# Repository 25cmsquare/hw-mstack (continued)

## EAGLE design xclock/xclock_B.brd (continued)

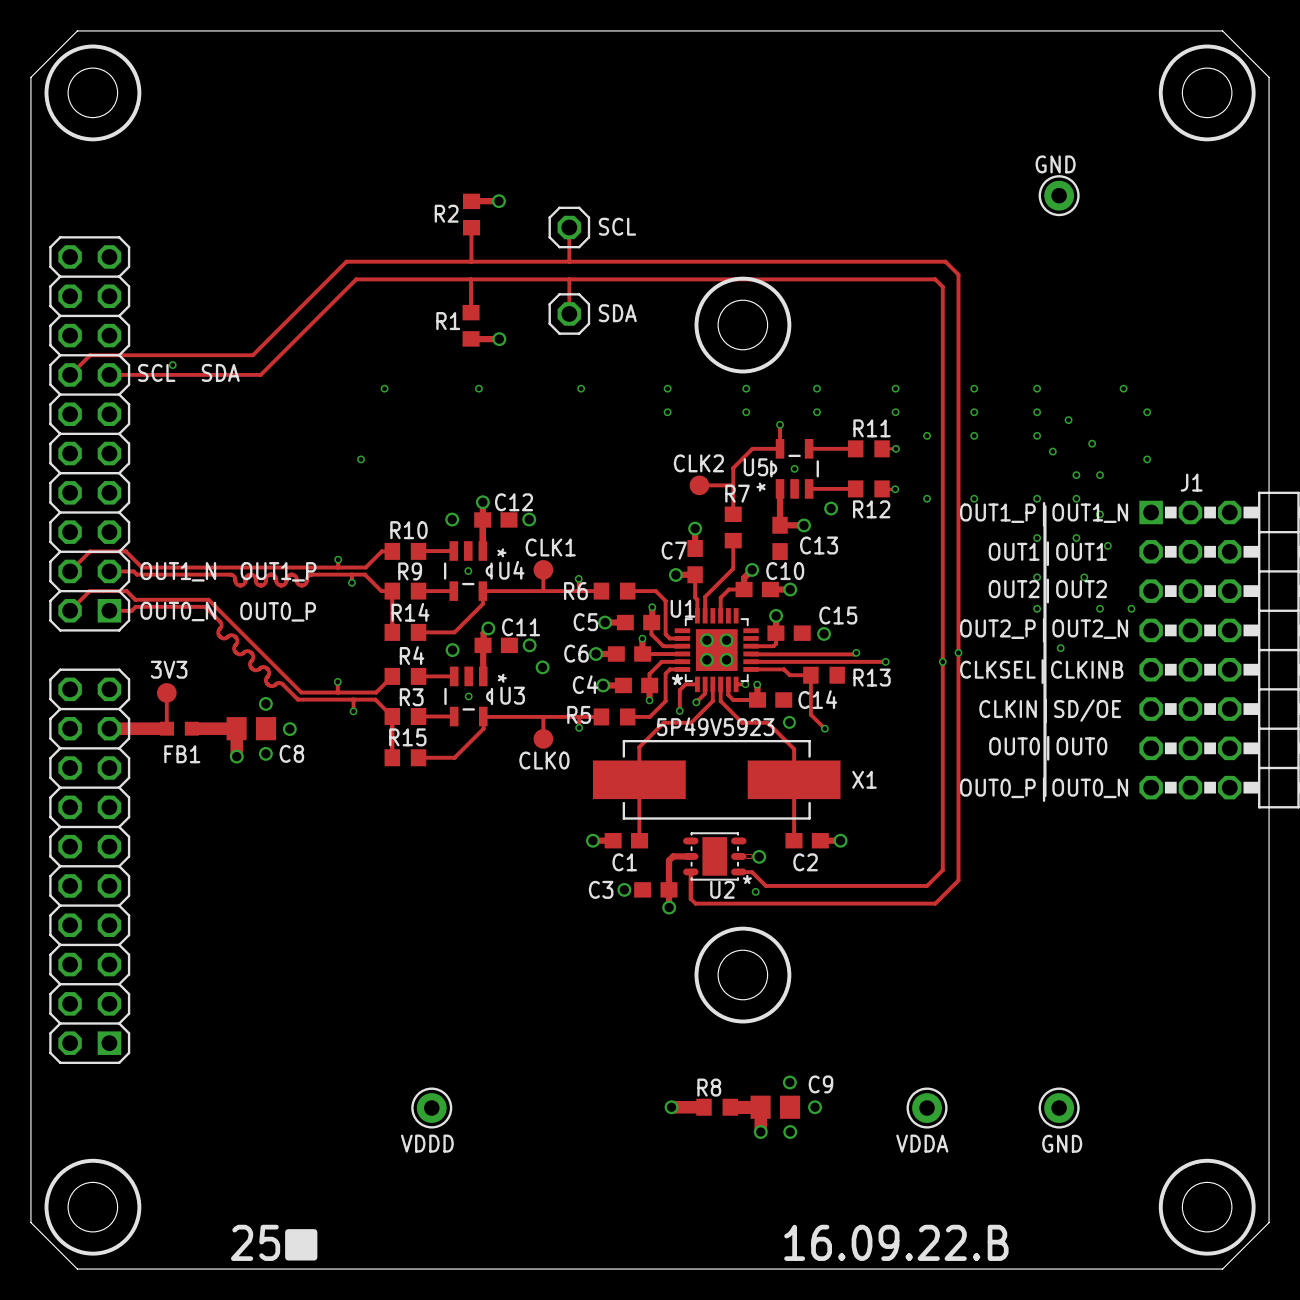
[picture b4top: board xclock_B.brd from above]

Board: 4 copper layers, 80.0 x 80.0 mm, 49 parts (0 on the bottom side), 30 nets.

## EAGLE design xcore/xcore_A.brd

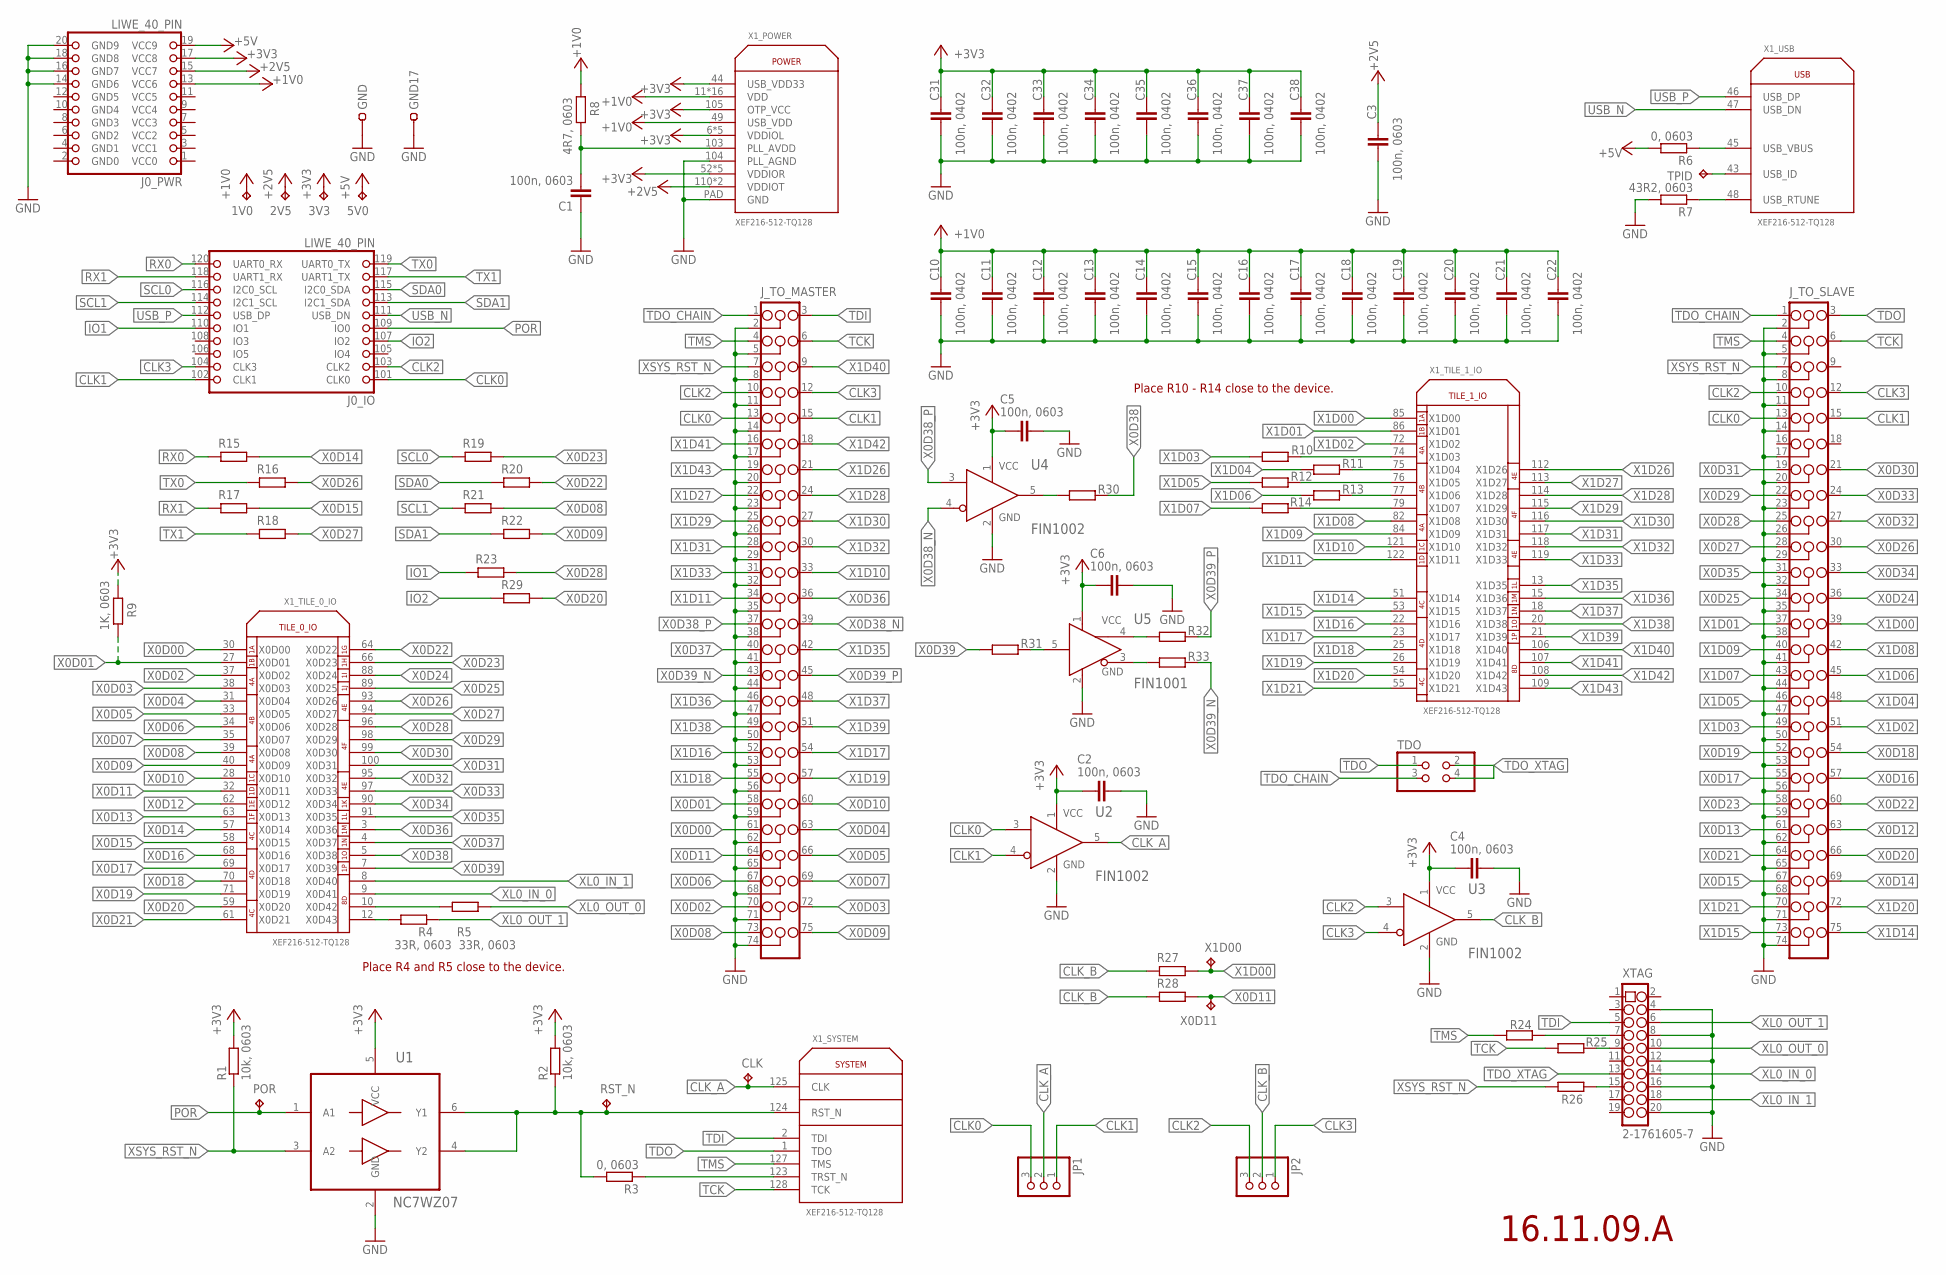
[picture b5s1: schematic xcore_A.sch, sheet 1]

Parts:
1V0, 2V5, 3V3, 5V0: TPTP14R; TP14R
C1, C2, C4, C5, C6: 100n, 0603; C0603
C3: 100n, 0603; C0402K
C10, C11, C12, C13, C14, C15, C16, C17, C18, C19, C20, C21, C22, C31, C32, C33, C34, C35, C36, C37, C38: 100n, 0402; C0402K
CLK: TPTP14R; TP14R
GND, GND17: TEST-22-MULTICOMP; TEST_1MM
J0: LIWE_40_PIN; LIWE_40_PIN_8X8
JP1, JP2: PINHD-1X3; 1X03
J_TO_MASTER: TSW-125-08-G-T-RA; 3X25/90/M
J_TO_SLAVE: TSW-125-08-G-T-RA; 3X25/90
POR: TPTP14R; TP14R
R1, R2: 10k, 0603; R0603
R3, R6: 0, 0603; R0603
R4, R5: 33R, 0603; R0603
R7: 43R2, 0603; R0603
R8: 4R7, 0603; R0603
R9: 1K, 0603; R0603
R10, R11, R12, R13, R14, R15, R16, R17, R18, R19, R20, R21, R22, R23, R24, R25, R26, R27, R28, R29, R30, R31, R32, R33: R-EU_R0603; R0603
RST_N: TPTP14R; TP14R
TDO: PINHD-2X2; 2X02
TPID: TPB1,27; B1,27
U1: NC7WZ07; SOT65P210X110-6N
U2, U3, U4: FIN1002; SOT95P280X140-5N
U5: FIN1001; SOT95P280X140-5N
X0D11, X1D00: TPTP14R; TP14R
X1: XEF216-512-TQ128; TQFP128
XTAG: 2-1761605-7; 2X10

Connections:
+1V0: 1V0.TP, C10.2, C11.2, C12.2, C13.2, C14.2, C15.2, C16.2, C17.2, C18.2, C19.2, C20.2, C21.2, C22.2, J0.13 (VCC6), R8.1, X1.11 (VDD), X1.16 (VDD), X1.17 (VDD), X1.24 (VDD), X1.36 (VDD), X1.41 (VDD), X1.49 (USB_VDD), X1.56 (VDD), X1.60 (VDD), X1.73 (VDD), X1.80 (VDD), X1.81 (VDD), X1.87 (VDD), X1.101 (VDD), X1.102 (VDD), X1.120 (VDD), X1.126 (VDD)
+2V5: 2V5.TP, C3.2, J0.15 (VCC7), X1.110 (VDDIOT), X1.111 (VDDIOT)
+3V3: 3V3.TP, C2.2, C4.2, C5.2, C6.2, C31.2, C32.2, C33.2, C34.2, C35.2, C36.2, C37.2, C38.2, J0.17 (VCC8), R1.2, R2.2, R9.1, U1.5 (VCC), U2.1 (VCC), U3.1 (VCC), U4.1 (VCC), U5.1 (VCC), X1.6 (VDDIOL), X1.14 (VDDIOL), X1.19 (VDDIOL), X1.29 (VDDIOL), X1.42 (VDDIOL), X1.44 (USB_VDD33), X1.52 (VDDIOR), X1.67 (VDDIOR), X1.78 (VDDIOR), X1.83 (VDDIOR), X1.92 (VDDIOR), X1.105 (OTP_VCC)
+5V: 5V0.TP, J0.19 (VCC9), R6.2
CLK0: J0.101 (CLK0), JP1.3, J_TO_MASTER.13, J_TO_SLAVE.13, U2.3 (RIN+)
CLK1: J0.102 (CLK1), JP1.1, J_TO_MASTER.15, J_TO_SLAVE.15, U2.4 (RIN-)
CLK2: J0.103 (CLK2), JP2.3, J_TO_MASTER.10, J_TO_SLAVE.10, U3.3 (RIN+)
CLK3: J0.104 (CLK3), JP2.1, J_TO_MASTER.12, J_TO_SLAVE.12, U3.4 (RIN-)
CLK_A: CLK.TP, JP1.2, U2.5 (ROUT), X1.125 (CLK)
CLK_B: JP2.2, R27.1, R28.1, U3.5 (ROUT)
GND: C1.1, C2.1, C3.1, C4.1, C5.1, C6.1, C10.1, C11.1, C12.1, C13.1, C14.1, C15.1, C16.1, C17.1, C18.1, C19.1, C20.1, C21.1, C22.1, C31.1, C32.1, C33.1, C34.1, C35.1, C36.1, C37.1, C38.1, GND.1, GND17.1, J0.14 (GND6), J0.16 (GND7), J0.18 (GND8), J0.20 (GND9), J_TO_MASTER.2, J_TO_MASTER.5, J_TO_MASTER.8, J_TO_MASTER.11, J_TO_MASTER.14, J_TO_MASTER.17, J_TO_MASTER.20, J_TO_MASTER.23, J_TO_MASTER.26, J_TO_MASTER.29, J_TO_MASTER.32, J_TO_MASTER.35, J_TO_MASTER.38, J_TO_MASTER.41, J_TO_MASTER.44, J_TO_MASTER.47, J_TO_MASTER.50, J_TO_MASTER.53, J_TO_MASTER.56, J_TO_MASTER.59, J_TO_MASTER.62, J_TO_MASTER.65, J_TO_MASTER.68, J_TO_MASTER.71, J_TO_MASTER.74, J_TO_SLAVE.2, J_TO_SLAVE.5, J_TO_SLAVE.8, J_TO_SLAVE.11, J_TO_SLAVE.14, J_TO_SLAVE.17, J_TO_SLAVE.20, J_TO_SLAVE.23, J_TO_SLAVE.26, J_TO_SLAVE.29, J_TO_SLAVE.32, J_TO_SLAVE.35, J_TO_SLAVE.38, J_TO_SLAVE.41, J_TO_SLAVE.44, J_TO_SLAVE.47, J_TO_SLAVE.50, J_TO_SLAVE.53, J_TO_SLAVE.56, J_TO_SLAVE.59, J_TO_SLAVE.62, J_TO_SLAVE.65, J_TO_SLAVE.68, J_TO_SLAVE.71, J_TO_SLAVE.74, R7.2, U1.2 (GND), U2.2 (GND), U3.2 (GND), U4.2 (GND), U5.2 (GND), X1.104 (PLL_AGND), X1.PAD (GND), XTAG.4, XTAG.8, XTAG.12, XTAG.16, XTAG.20
IO1: J0.110 (IO1), R23.1
IO2: J0.107 (IO2), R29.1
unnamed: R10.2, X1.74 (X1D03)
unnamed: R11.2, X1.75 (X1D04)
unnamed: R12.2, X1.76 (X1D05)
unnamed: R13.2, X1.77 (X1D06)
unnamed: R14.2, X1.79 (X1D07)
unnamed: R30.1, U4.5 (ROUT)
unnamed: R31.2, U5.5 (RIN)
unnamed: R32.1, U5.4 (ROUT+)
unnamed: R33.1, U5.3 (ROUT-)
PLL_AVDD: C1.2, R8.2, X1.103 (PLL_AVDD)
POR: J0.109 (IO0), POR.TP, U1.1 (A1)
RST_N: R2.1, R3.2, RST_N.TP, U1.4 (Y2), U1.6 (Y1), X1.124 (RST_N)
RX0: J0.120 (UART0_RX), R15.1
RX1: J0.118 (UART1_RX), R17.1
SCL0: J0.116 (I2C0_SCL), R19.1
SCL1: J0.114 (I2C1_SCL), R21.1
SDA0: J0.115 (I2C0_SDA), R20.1
SDA1: J0.113 (I2C1_SDA), R22.1
TCK: J_TO_MASTER.6, J_TO_SLAVE.6, R25.1, X1.128 (TCK)
TCK_: R25.2, XTAG.9
TDI: J_TO_MASTER.3, X1.2 (TDI), XTAG.5
TDO: J_TO_SLAVE.3, TDO.1, X1.1 (TDO)
TDO_CHAIN: J_TO_MASTER.1, J_TO_SLAVE.1, TDO.3
TDO_XTAG: TDO.2, TDO.4, XTAG.13
TMS: J_TO_MASTER.4, J_TO_SLAVE.4, R24.1, X1.127 (TMS)
TMS_: R24.2, XTAG.7
TRST_N: R3.1, X1.123 (TRST_N)
TX0: J0.119 (UART0_TX), R16.1
TX1: J0.117 (UART1_TX), R18.1
USB_ID: TPID.TP, X1.43 (USB_ID)
USB_N: J0.111 (USB_DN), X1.47 (USB_DN)
USB_P: J0.112 (USB_DP), X1.46 (USB_DP)
USB_RTUNE: R7.1, X1.48 (USB_RTUNE)
USB_VBUS: R6.1, X1.45 (USB_VBUS)
X0D00: J_TO_MASTER.61, X1.30 (X0D00)
X0D01: J_TO_MASTER.58, R9.2, X1.27 (X0D01)
X0D02: J_TO_MASTER.70, X1.37 (X0D02)
X0D03: J_TO_MASTER.72, X1.38 (X0D03)
X0D04: J_TO_MASTER.63, X1.31 (X0D04)
X0D05: J_TO_MASTER.66, X1.33 (X0D05)
X0D06: J_TO_MASTER.67, X1.34 (X0D06)
X0D07: J_TO_MASTER.69, X1.35 (X0D07)
X0D08: J_TO_MASTER.73, R21.2, X1.39 (X0D08)
X0D09: J_TO_MASTER.75, R22.2, X1.40 (X0D09)
X0D10: J_TO_MASTER.60, X1.28 (X0D10)
X0D11: J_TO_MASTER.64, R28.2, X0D11.TP, X1.32 (X0D11)
X0D12: J_TO_SLAVE.63, X1.62 (X0D12)
X0D13: J_TO_SLAVE.61, X1.63 (X0D13)
X0D14: J_TO_SLAVE.69, R15.2, X1.57 (X0D14)
X0D15: J_TO_SLAVE.67, R17.2, X1.58 (X0D15)
X0D16: J_TO_SLAVE.57, X1.68 (X0D16)
X0D17: J_TO_SLAVE.55, X1.69 (X0D17)
X0D18: J_TO_SLAVE.54, X1.70 (X0D18)
X0D19: J_TO_SLAVE.52, X1.71 (X0D19)
X0D20: J_TO_SLAVE.66, R29.2, X1.59 (X0D20)
X0D21: J_TO_SLAVE.64, X1.61 (X0D21)
X0D22: J_TO_SLAVE.60, R20.2, X1.64 (X0D22)
X0D23: J_TO_SLAVE.58, R19.2, X1.66 (X0D23)
X0D24: J_TO_SLAVE.36, X1.88 (X0D24)
X0D25: J_TO_SLAVE.34, X1.89 (X0D25)
X0D26: J_TO_SLAVE.30, R16.2, X1.93 (X0D26)
X0D27: J_TO_SLAVE.28, R18.2, X1.94 (X0D27)
X0D28: J_TO_SLAVE.25, R23.2, X1.96 (X0D28)
X0D29: J_TO_SLAVE.22, X1.98 (X0D29)
X0D30: J_TO_SLAVE.21, X1.99 (X0D30)
X0D31: J_TO_SLAVE.19, X1.100 (X0D31)
X0D32: J_TO_SLAVE.27, X1.95 (X0D32)
X0D33: J_TO_SLAVE.24, X1.97 (X0D33)
X0D34: J_TO_SLAVE.33, X1.90 (X0D34)
X0D35: J_TO_SLAVE.31, X1.91 (X0D35)
X0D36: J_TO_MASTER.36, X1.3 (X0D36)
X0D37: J_TO_MASTER.40, X1.4 (X0D37)
X0D38: R30.2, X1.5 (X0D38)
X0D38_N: J_TO_MASTER.39, U4.4 (RIN-)
X0D38_P: J_TO_MASTER.37, U4.3 (RIN+)
X0D39: R31.1, X1.7 (X0D39)
X0D39_N: J_TO_MASTER.43, R33.2
X0D39_P: J_TO_MASTER.45, R32.2
X0D42: R5.2, X1.10 (X0D42)
X0D43: R4.2, X1.12 (X0D43)
X1D00: J_TO_SLAVE.39, R27.2, X1.85 (X1D00), X1D00.TP
X1D01: J_TO_SLAVE.37, X1.86 (X1D01)
X1D02: J_TO_SLAVE.51, X1.72 (X1D02)
X1D03: J_TO_SLAVE.49, R10.1
X1D04: J_TO_SLAVE.48, R11.1
X1D05: J_TO_SLAVE.46, R12.1
X1D06: J_TO_SLAVE.45, R13.1
X1D07: J_TO_SLAVE.43, R14.1
X1D08: J_TO_SLAVE.42, X1.82 (X1D08)
X1D09: J_TO_SLAVE.40, X1.84 (X1D09)
X1D10: J_TO_MASTER.33, X1.121 (X1D10)
X1D11: J_TO_MASTER.34, X1.122 (X1D11)
X1D14: J_TO_SLAVE.75, X1.51 (X1D14)
X1D15: J_TO_SLAVE.73, X1.53 (X1D15)
X1D16: J_TO_MASTER.52, X1.22 (X1D16)
X1D17: J_TO_MASTER.54, X1.23 (X1D17)
X1D18: J_TO_MASTER.55, X1.25 (X1D18)
X1D19: J_TO_MASTER.57, X1.26 (X1D19)
X1D20: J_TO_SLAVE.72, X1.54 (X1D20)
X1D21: J_TO_SLAVE.70, X1.55 (X1D21)
X1D26: J_TO_MASTER.21, X1.112 (X1D26)
X1D27: J_TO_MASTER.22, X1.113 (X1D27)
X1D28: J_TO_MASTER.24, X1.114 (X1D28)
X1D29: J_TO_MASTER.25, X1.115 (X1D29)
X1D30: J_TO_MASTER.27, X1.116 (X1D30)
X1D31: J_TO_MASTER.28, X1.117 (X1D31)
X1D32: J_TO_MASTER.30, X1.118 (X1D32)
X1D33: J_TO_MASTER.31, X1.119 (X1D33)
X1D35: J_TO_MASTER.42, X1.13 (X1D35)
X1D36: J_TO_MASTER.46, X1.15 (X1D36)
X1D37: J_TO_MASTER.48, X1.18 (X1D37)
X1D38: J_TO_MASTER.49, X1.20 (X1D38)
X1D39: J_TO_MASTER.51, X1.21 (X1D39)
X1D40: J_TO_MASTER.9, X1.106 (X1D40)
X1D41: J_TO_MASTER.16, X1.107 (X1D41)
X1D42: J_TO_MASTER.18, X1.108 (X1D42)
X1D43: J_TO_MASTER.19, X1.109 (X1D43)
XL0_IN_0: X1.9 (X0D41), XTAG.14
XL0_IN_1: X1.8 (X0D40), XTAG.18
XL0_OUT_0: R5.1, XTAG.10
XL0_OUT_1: R4.1, XTAG.6
XSYS_RST_N: J_TO_MASTER.7, J_TO_SLAVE.7, R1.1, R26.1, U1.3 (A2)
XSYS_RST_N_: R26.2, XTAG.15

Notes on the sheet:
16.11.09.A
Place R4 and R5 close to the device.
Place R10 - R14 close to the device.

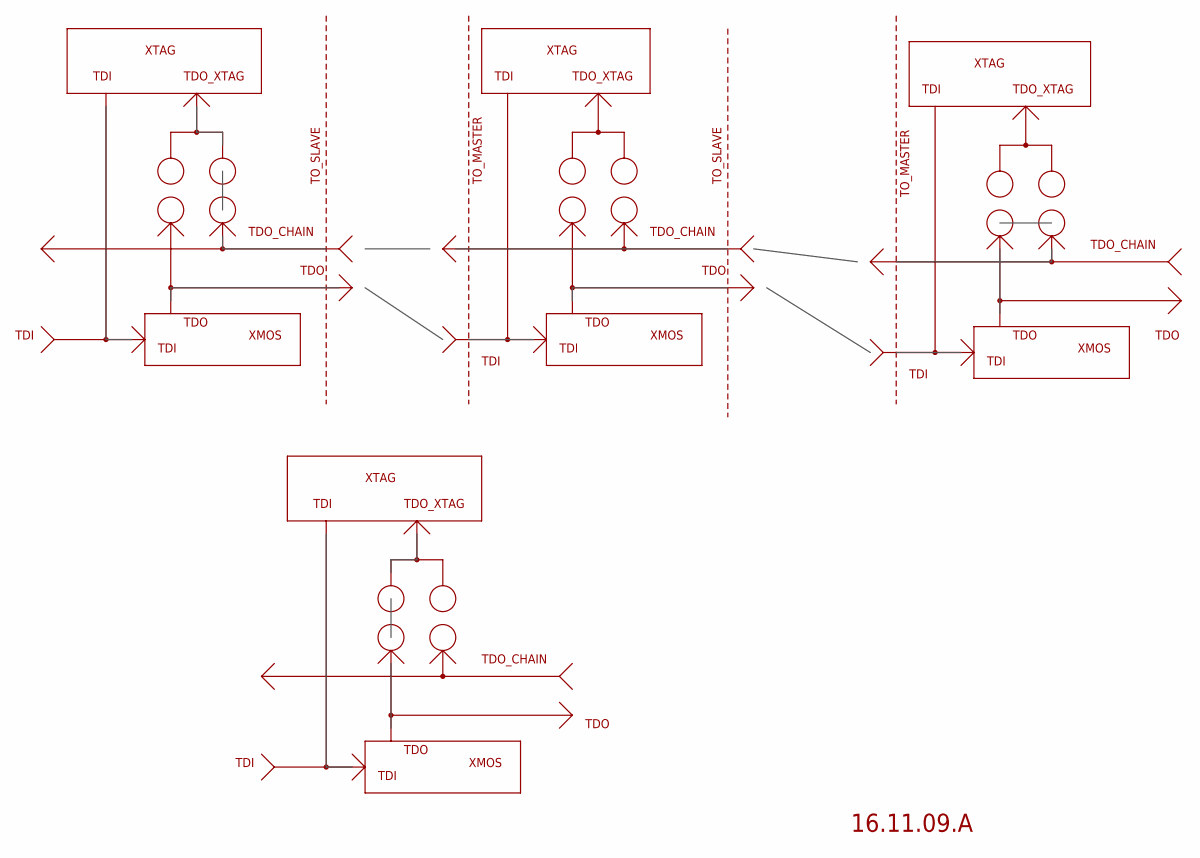
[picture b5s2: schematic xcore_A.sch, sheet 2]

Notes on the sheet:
16.11.09.A
XTAG
XMOS
TDO_XTAG
TDI
TDO
TDO_CHAIN
TO_SLAVE
TO_MASTER

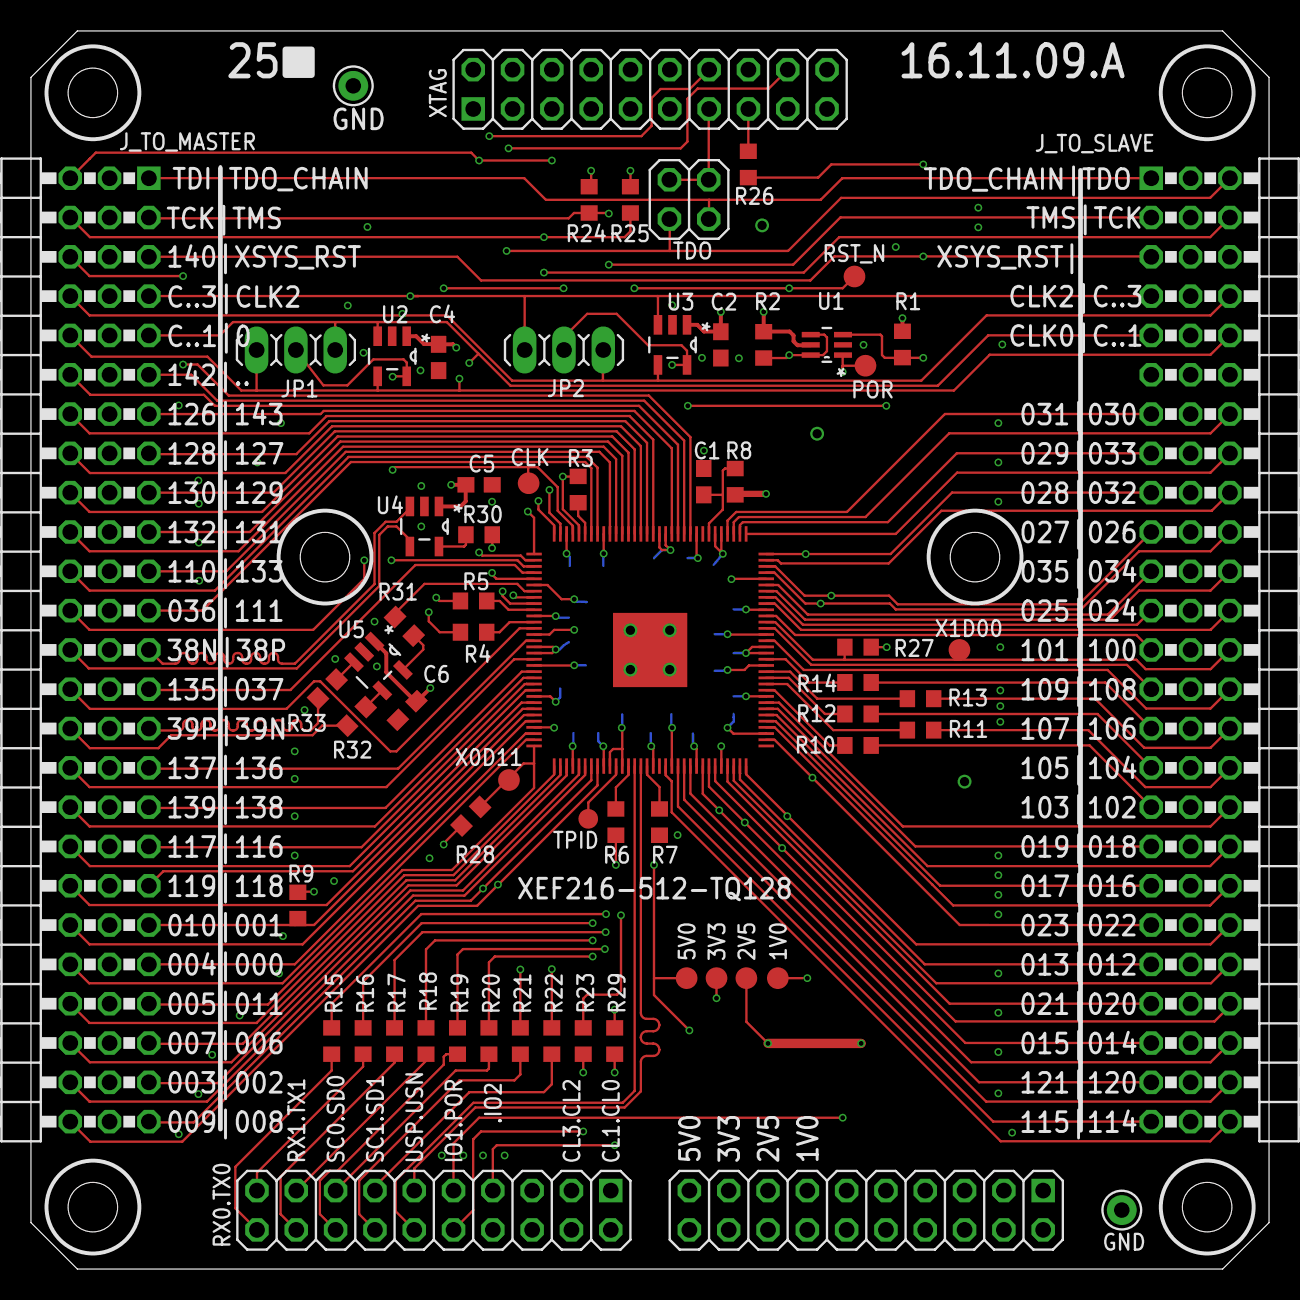
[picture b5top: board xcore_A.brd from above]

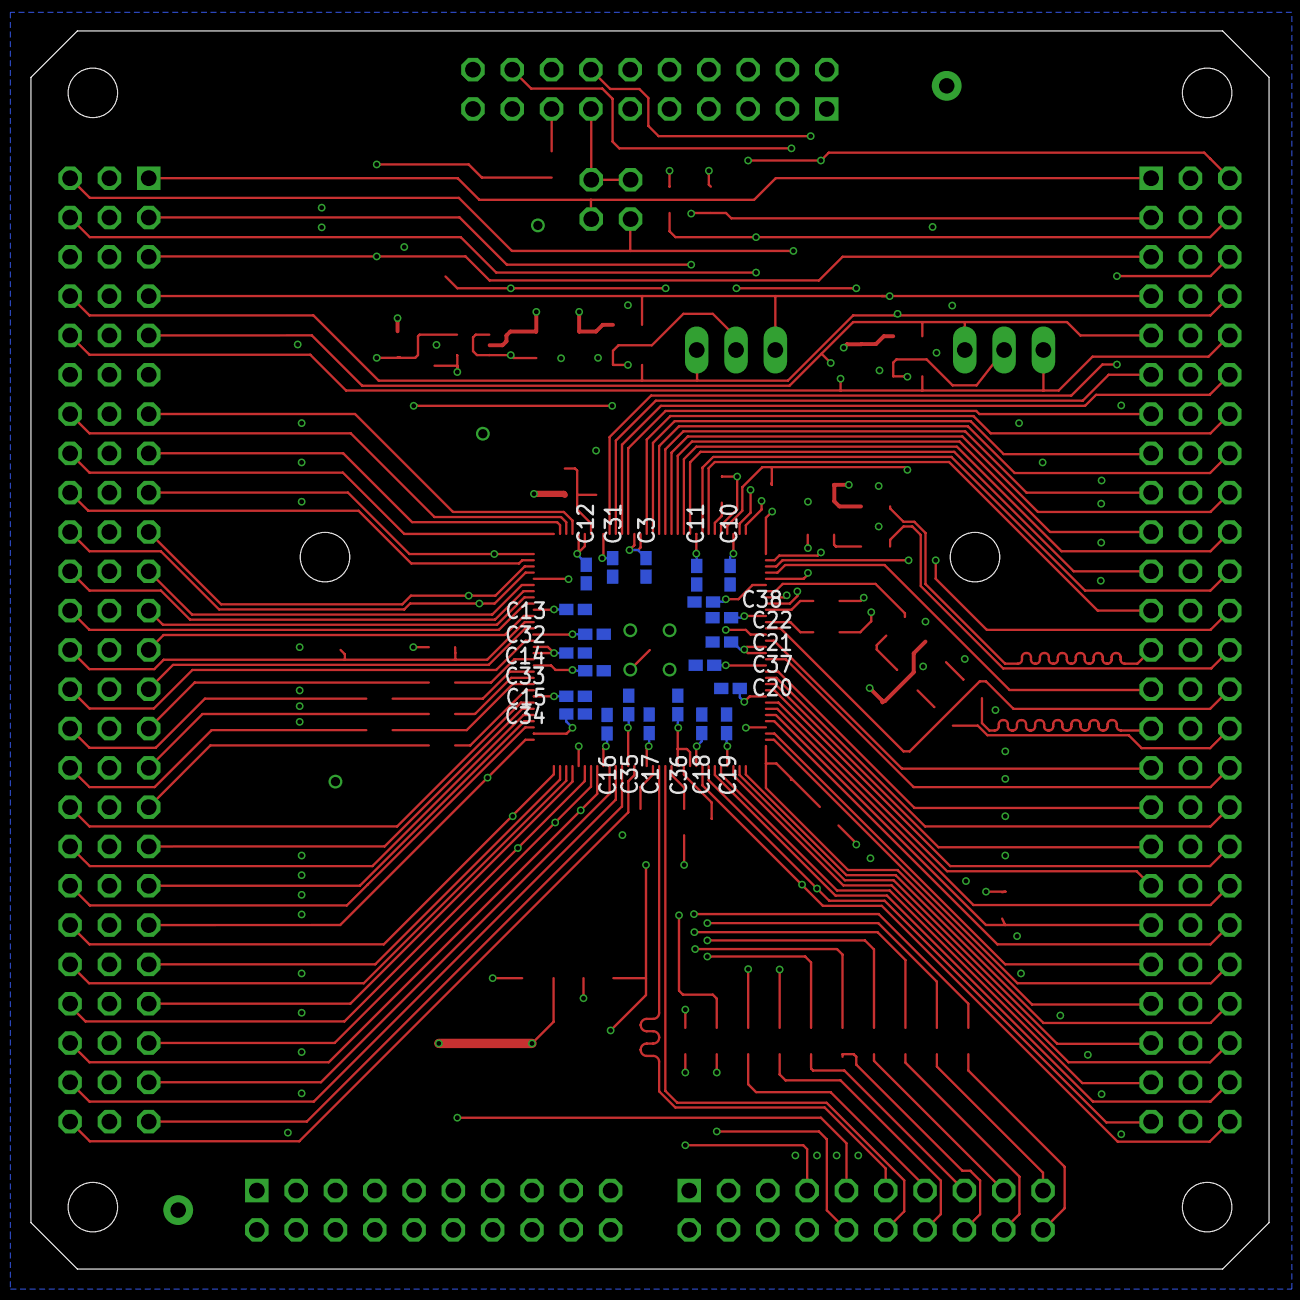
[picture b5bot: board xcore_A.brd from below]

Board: 4 copper layers, 80.0 x 80.0 mm, 85 parts (22 on the bottom side), 136 nets.

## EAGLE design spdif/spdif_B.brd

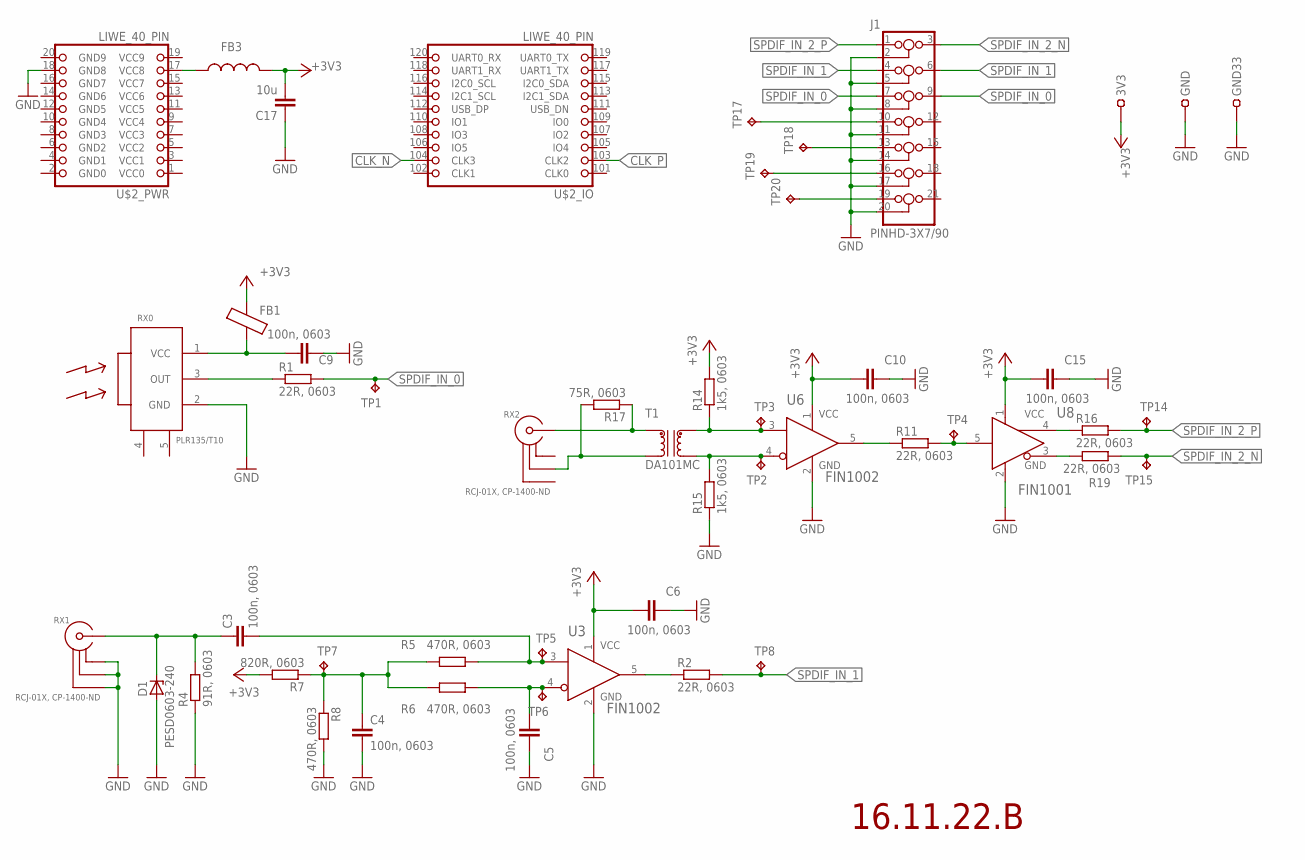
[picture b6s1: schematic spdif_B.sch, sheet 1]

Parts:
3V3: TEST-22-MULTICOMP; TEST_1MM
C3, C4, C5, C6, C9, C10, C15: 100n, 0603; C0603
C17: 10u; C0805
D1: PESD0603-240; L0603
FB1: FB_0603; L0603
FB3: L0603(1608); L0603
GND, GND33: TEST-22-MULTICOMP; TEST_1MM
J1: PINHD-3X7/90; 3X07/90
R1, R2, R11, R16, R19: 22R, 0603; R0603
R4: 91R, 0603; R0603
R5, R6, R8: 470R, 0603; R0603
R7: 820R, 0603; R0603
R14, R15: 1k5, 0603; R0603
R17: 75R, 0603; R0603
RX0: PLR135/T10; PLR135_T10
RX1, RX2: RCJ-01X, CP-1400-ND; RCJ-01X
T1: DA101MC
TP1, TP2, TP3, TP4, TP5, TP6, TP7, TP8, TP14, TP15, TP17, TP18, TP19, TP20: TPB1,27; B1,27
U3, U6: FIN1002; SOT95P280X140-5N
U8: FIN1001; SOT95P280X140-5N
U$2: LIWE_40_PIN; LIWE_40_PIN_8X8

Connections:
+3V3: 3V3.1, C6.2, C10.2, C15.2, C17.2, FB1.2, FB3.2, R7.2, R14.2, U3.1 (VCC), U6.1 (VCC), U8.1 (VCC); also elsewhere on the board
CLK_N: U$2.104 (CLK3); also elsewhere on the board
CLK_P: U$2.103 (CLK2); also elsewhere on the board
GND: C4.2, C5.1, C6.1, C9.1, C10.1, C15.1, C17.1, D1.1 (A), GND.1, GND33.1, J1.2, J1.5, J1.8, J1.11, J1.14, J1.17, J1.20, R4.1, R8.2, R15.1, RX0.2 (GND), RX1.20 (GND1), RX1.21 (GND2), RX1.22 (GND3), U3.2 (GND), U6.2 (GND), U8.2 (GND), U$2.18 (GND8); also elsewhere on the board
unnamed: R11.2, TP4.TP, U8.5 (RIN)
unnamed: R16.1, U8.4 (ROUT+)
unnamed: R2.1, U3.5 (ROUT)
unnamed: C3.2, R5.1, TP5.TP, U3.3 (RIN+)
unnamed: C9.2, FB1.1, RX0.1 (VCC)
unnamed: C3.1, D1.2 (C), R4.2, RX1.1 (SIG)
unnamed: R19.1, U8.3 (ROUT-)
unnamed: C4.1, R5.2, R6.2, R7.1, R8.1, TP7.TP
unnamed: C5.2, R6.1, TP6.TP, U3.4 (RIN-)
unnamed: J1.10, TP17.TP
unnamed: R15.2, T1.4, TP2.TP, U6.4 (RIN-)
unnamed: R14.1, T1.6, TP3.TP, U6.3 (RIN+)
unnamed: J1.13, TP18.TP
unnamed: J1.16, TP19.TP
unnamed: R17.2, RX2.21 (GND2), T1.3
unnamed: R17.1, RX2.1 (SIG), T1.1
unnamed: J1.19, TP20.TP
unnamed: FB3.1, U$2.17 (VCC8)
SPDIF0_IN: R1.1, RX0.3 (OUT)
SPDIF_IN_0: J1.7, J1.9, R1.2, TP1.TP
SPDIF_IN_1: J1.4, J1.6, R2.2, TP8.TP
SPDIF_IN_2_N: J1.3, R19.2, TP15.TP
SPDIF_IN_2_P: J1.1, R16.2, TP14.TP
U6_OUT: R11.1, U6.5 (ROUT)

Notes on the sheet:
16.11.22.B

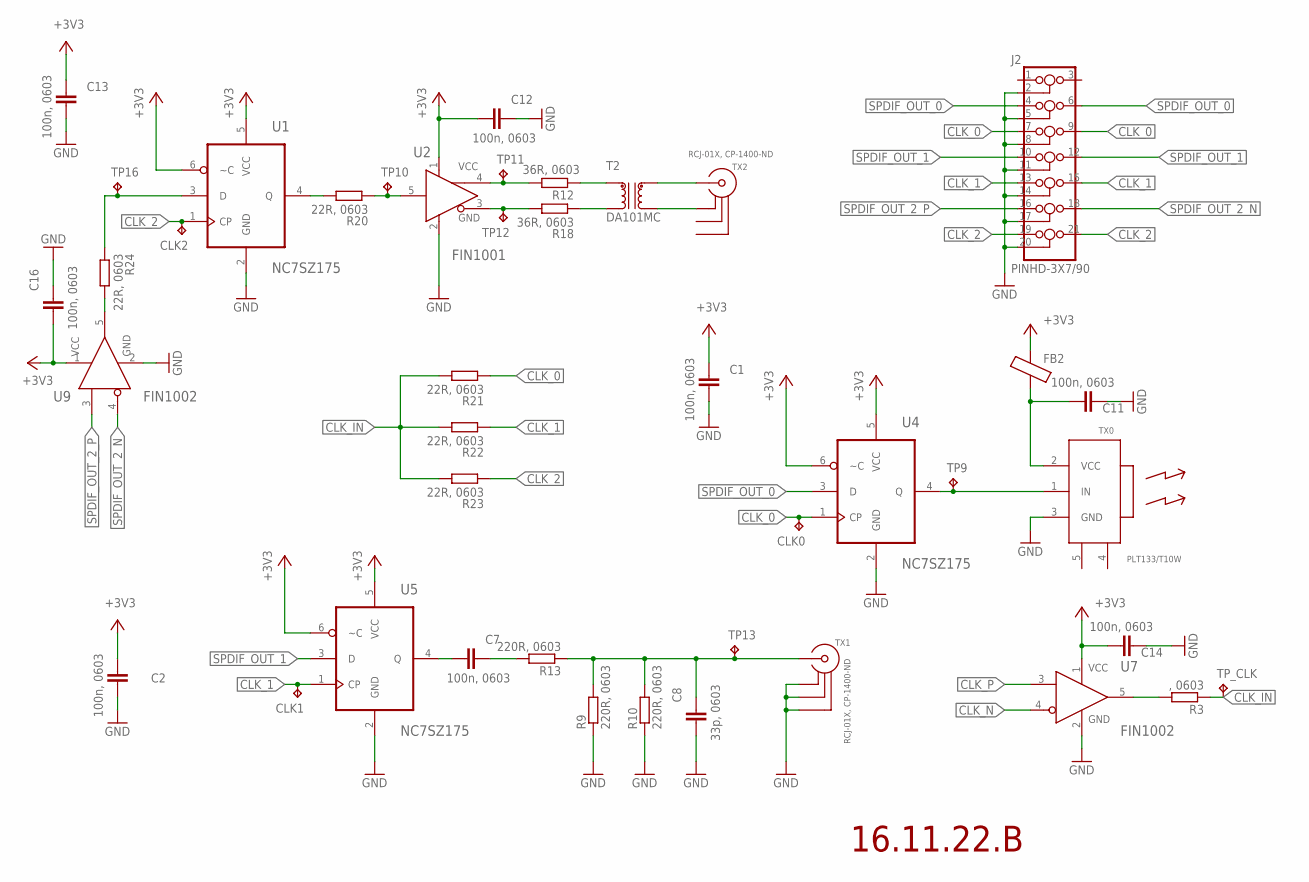
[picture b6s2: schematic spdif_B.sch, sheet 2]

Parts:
C1, C2, C7, C11, C12, C13, C14, C16: 100n, 0603; C0603
C8: 33p, 0603; C0603
CLK0, CLK1, CLK2: TPB1,27; B1,27
FB2: FB_0603; L0603
J2: PINHD-3X7/90; 3X07/90
R3: , 0603; R0603
R9, R10, R13: 220R, 0603; R0603
R12, R18: 36R, 0603; R0603
R20, R21, R22, R23, R24: 22R, 0603; R0603
T2: DA101MC
TP9, TP10, TP11, TP12, TP13, TP16: TPB1,27; B1,27
TP_CLK: TPB1,27; B1,27
TX0: PLT133/T10W; PLT133_T10W
TX1, TX2: RCJ-01X, CP-1400-ND; RCJ-01X
U1, U4, U5: NC7SZ175; SOT65P210X110-6N
U2: FIN1001; SOT95P280X140-5N
U7, U9: FIN1002; SOT95P280X140-5N

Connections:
+3V3: C1.2, C2.2, C12.2, C13.2, C14.2, C16.2, FB2.2, U1.5 (VCC), U1.6 (~C), U2.1 (VCC), U4.5 (VCC), U4.6 (~C), U5.5 (VCC), U5.6 (~C), U7.1 (VCC), U9.1 (VCC); also elsewhere on the board
CLK_0: CLK0.TP, J2.7, J2.9, R21.1, U4.1 (CP)
CLK_1: CLK1.TP, J2.13, J2.15, R22.1, U5.1 (CP)
CLK_2: CLK2.TP, J2.19, J2.21, R23.1, U1.1 (CP)
CLK_IN: R3.1, R21.2, R22.2, R23.2, TP_CLK.TP
CLK_N: U7.4 (RIN-); also elsewhere on the board
CLK_P: U7.3 (RIN+); also elsewhere on the board
DA_N: R18.1, T2.3
DA_P: R12.1, T2.1
FIN_IN: R20.1, TP10.TP, U2.5 (RIN)
FIN_OUT_N: R18.2, TP12.TP, U2.3 (ROUT-)
FIN_OUT_P: R12.2, TP11.TP, U2.4 (ROUT+)
GND: C1.1, C2.1, C8.2, C11.1, C12.1, C13.1, C14.1, C16.1, J2.2, J2.5, J2.8, J2.11, J2.14, J2.17, J2.20, R9.1, R10.1, TX0.3 (GND), TX1.20 (GND1), TX1.21 (GND2), TX1.22 (GND3), U1.2 (GND), U2.2 (GND), U4.2 (GND), U5.2 (GND), U7.2 (GND), U9.2 (GND); also elsewhere on the board
unnamed: R24.2, U9.5 (ROUT)
unnamed: R3.2, U7.5 (ROUT)
unnamed: R24.1, TP16.TP, U1.3 (D)
unnamed: C7.1, R13.2
unnamed: C7.2, U5.4 (Q)
Q: R20.2, U1.4 (Q)
SPDIF_OUT_0: J2.4, J2.6, U4.3 (D)
SPDIF_OUT_1: J2.10, J2.12, U5.3 (D)
SPDIF_OUT_2_N: J2.18, U9.4 (RIN-)
SPDIF_OUT_2_P: J2.16, U9.3 (RIN+)
TX0_IN: TP9.TP, TX0.1 (IN), U4.4 (Q)
TX0_VCC: C11.2, FB2.1, TX0.2 (VCC)
TX1_IN: C8.1, R9.2, R10.2, R13.1, TP13.TP, TX1.1 (SIG)
TX2_N: T2.4, TX2.20 (GND1)
TX2_P: T2.6, TX2.1 (SIG)

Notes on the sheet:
16.11.22.B

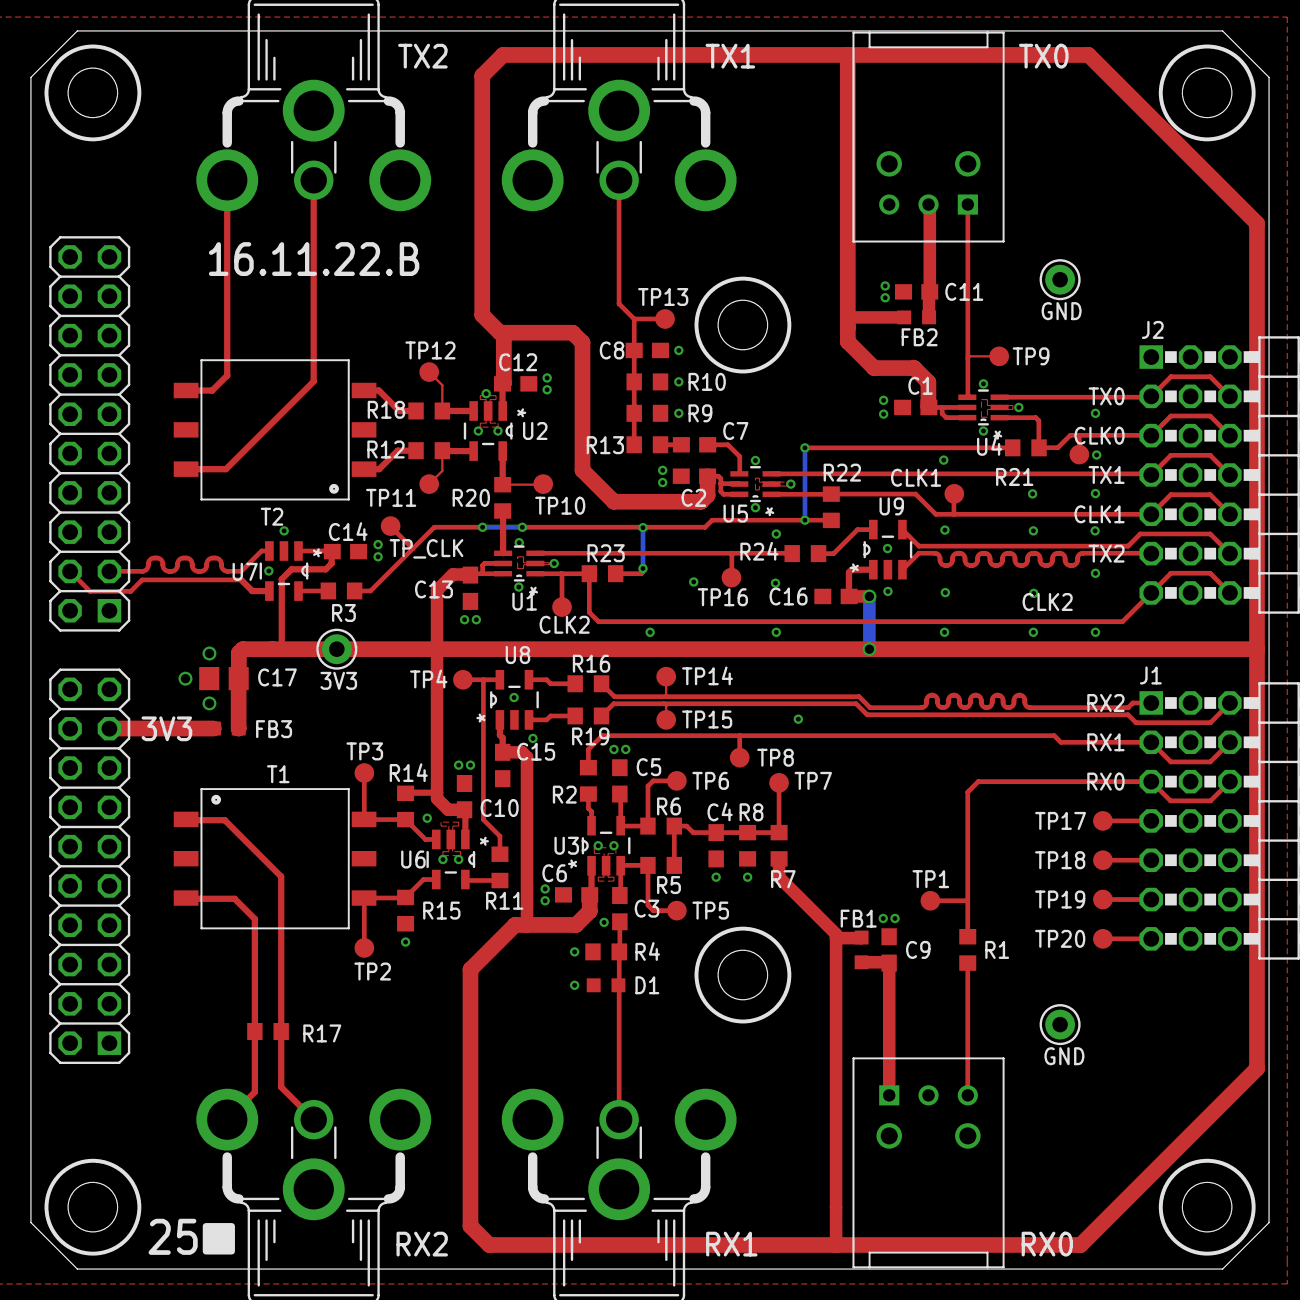
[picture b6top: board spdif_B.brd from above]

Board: 2 copper layers, 80.0 x 80.0 mm, 92 parts (0 on the bottom side), 52 nets.

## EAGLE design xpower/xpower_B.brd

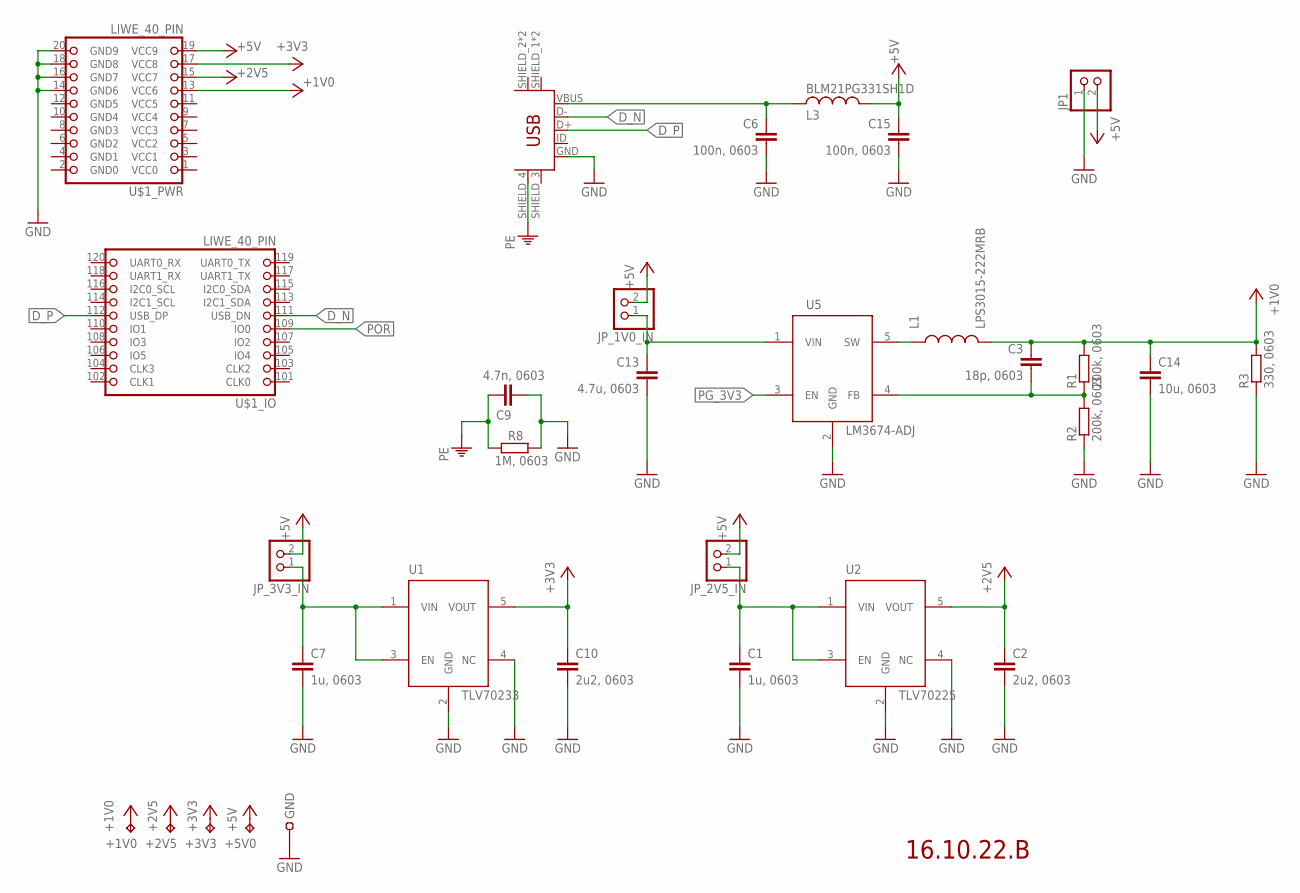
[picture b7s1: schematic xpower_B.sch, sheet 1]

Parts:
+1V0, +2V5, +3V3, +5V0: TPTP14R; TP14R
C1, C7: 1u, 0603; C0603
C2, C10: 2u2, 0603; C0603
C3: 18p, 0603; C0603
C6, C15: 100n, 0603; C0603
C9: 4.7n, 0603; C0603
C13: 4.7u, 0603; C0603
C14: 10u, 0603; C0603
GND: TEST-22-MULTICOMP; TEST_1MM
JP1: PINHD-1X2; 1X02
JP_1V0_IN, JP_2V5_IN, JP_3V3_IN: PINHD-1X2; 1X02
L1: LPS3015-222MRB; LPS3015
L3: BLM21PG331SH1D; R0805
R1, R2: 200k, 0603; R0603
R3: 330, 0603; R0603
R8: 1M, 0603; R0603
U1: TLV70233; SOT-23-5
U2: TLV70225; SOT-23-5
U5: LM3674-ADJ; SOT-23-5
U$1: LIWE_40_PIN; LIWE_40_PIN_8X8
U$5: ZX62D-B-5PA8

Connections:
+1V0: +1V0.TP, C3.1, C14.1, L1.P2 (2), R1.2, R3.2, U$1.13 (VCC6); also elsewhere on the board
+2V5: +2V5.TP, C2.1, U2.5 (VOUT), U$1.15 (VCC7)
+3V3: +3V3.TP, C10.1, U1.5 (VOUT), U$1.17 (VCC8); also elsewhere on the board
+5V: +5V0.TP, C15.1, JP1.2, JP_1V0_IN.2, JP_2V5_IN.2, JP_3V3_IN.2, L3.1, U$1.19 (VCC9)
D_N: U$1.111 (USB_DN), U$5.D-
D_P: U$1.112 (USB_DP), U$5.D+
FB: C3.2, R1.1, R2.2, U5.4 (FB)
GND: C1.2, C2.2, C6.2, C7.2, C9.2, C10.2, C13.2, C14.2, C15.2, GND.1, JP1.1, R2.1, R3.1, R8.1, U1.2 (GND), U1.4 (NC), U2.2 (GND), U2.4 (NC), U5.2 (GND), U$1.14 (GND6), U$1.16 (GND7), U$1.18 (GND8), U$1.20 (GND9), U$5.GND; also elsewhere on the board
L: L1.P1 (1), U5.5 (SW)
unnamed: C1.1, JP_2V5_IN.1, U2.1 (VIN), U2.3 (EN)
unnamed: C7.1, JP_3V3_IN.1, U1.1 (VIN), U1.3 (EN)
unnamed: C13.1, JP_1V0_IN.1, U5.1 (VIN)
PE: C9.1, R8.2, U$5.SHIELD_4 (MTN4)
PG_3V3: U5.3 (EN); also elsewhere on the board
POR: U$1.109 (IO0); also elsewhere on the board
VBUS: C6.1, L3.2, U$5.VBUS

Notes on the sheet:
16.10.22.B
